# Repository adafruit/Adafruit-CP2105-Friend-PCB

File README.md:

## Adafruit CP2105 Friend - USB to Dual UART Serial Converters PCB

<a href="http://www.adafruit.com/products/6065"><br/>
Click here to purchase one from the Adafruit shop</a>

PCB files for the Adafruit CP2105 Friend - USB to Dual UART Serial Converters. 

Format is EagleCAD schematic and board layout
* https://www.adafruit.com/product/6065

### Description

On our first Pentium 120 tower (purchased at PCs for Everyone on Thorndike st in Cambridge Mass) came with two DE-9 serial ports on the back: COM1 and COM2. Perfect for connecting a mouse and maybe a modem. Nowadays, long gone are the days of parallel ports and serial ports. Now the USB port reigns supreme! But USB is hard, and you just want to transfer your every-day serial data from two serial ports to a single USB port without the complexity of a hub. What now? Enter the Adafruit CP2105 Friend!

The CP2105 is very similar to the CP2102N. Except, instead of having a single serial UART port, it has two. One is 'standard' and one is 'enhanced' - you'll get both enumerated when plugging in this device, without any hub required!

The Enhanced port can do:

* Data formats supported:
- Data bits: 5, 6, 7, and 8
- Stop bits: 1, 1.5, and 2
- Parity: odd, even, mark, space, no parity
* Baud rates: 300 bps to 2.0 Mbps
* 320 Byte receive and transmit buffers
* Modem control signals: CTS, RTS, DTR, DSR and RI

The Standard port can do:

* Data format: 8 data bits, 1 Stop bit
Parity: Even, Odd, No parity
* Baud rates: 2400 bps to 921600 bps
* 288 Byte receive and transmit buffers
* Modem control signals: CTS, RTS, DTR, DSR and RI

Like the CP2102N breakout, we have USB C connector and the same overall shape, but there are some significant changes. The pins are going to be totally different because we have two UARTs, one on either 'side' of the board. The left side is the Enhanced port, right side is the Standard port. We don't have extra GPIO pads and no indicator LEDs. Also the bottom row is a 'minimal' output of just the two RX/TX pads and power pins.

We like the CP210x series because it has better driver support than the CH340 and can do very high speeds, and variable speeds without stability issues. Compared to the FT232RL and FT231X, the CP210x has the same capabilities or better, at a great price! 

Each order comes with a fully assembled and tested board. We give you some pin header strip, solder it in to plug it into a breadboard and get access to all the pins.

For Linux you won't need a driver. For Windows, it will automatically grab the driver from Windows Update. For Mac OS X you can check out SiLabs driver page for the latest and greatest.

### License

Adafruit invests time and resources providing this open source design, please support Adafruit and open-source hardware by purchasing products from [Adafruit](https://www.adafruit.com)!

Designed by Limor Fried/Ladyada for Adafruit Industries.

Creative Commons Attribution/Share-Alike, all text above must be included in any redistribution. 
See license.txt for additional details.

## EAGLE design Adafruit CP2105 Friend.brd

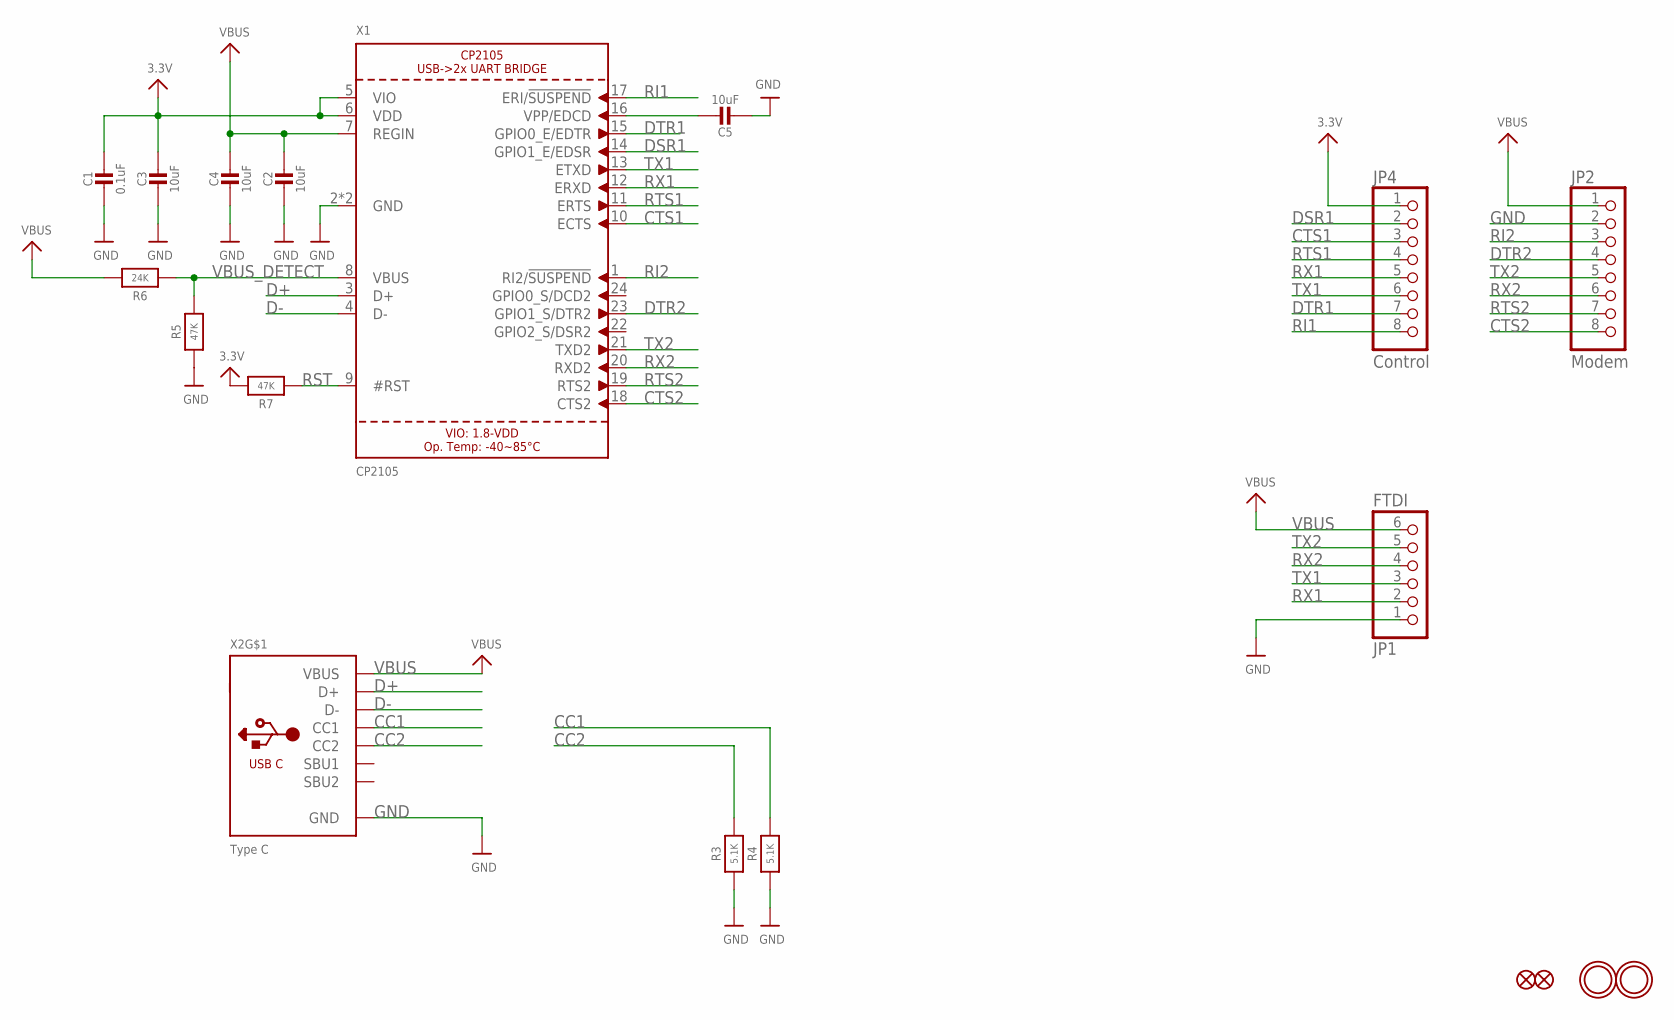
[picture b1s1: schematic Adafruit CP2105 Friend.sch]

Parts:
C1: 0.1uF; 0603-NO
C2, C3, C4, C5: 10uF; 0805-NO
FID1, FID2: FIDUCIAL_0.5MM
JP1: FTDI; 1X06_ROUND_70
JP2: Modem; 1X08_ROUND_70
JP4: Control; 1X08_ROUND_70
R3, R4: 5.1K; 0603-NO
R5, R7: 47K; 0603-NO
R6: 24K; 0603-NO
U$18, U$19: MOUNTINGHOLE2.0; MOUNTINGHOLE_2.0_PLATED
X1: CP2105; QFN24_4MM
X2: Type C; USB_C_CUSB31-CFM2AX-01-X

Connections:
3.3V: C1.1, C3.1, JP4.1, R7.2, X1.5 (VIO), X1.6 (VDD)
CC1: R4.2, X2.A5 (CC1)
CC2: R3.2, X2.B5 (CC2)
CTS1: JP4.3, X1.10 (ECTS)
CTS2: JP2.8, X1.18 (CTS2)
D+: X1.3 (D+), X2.A6 (D+), X2.B6 (D+)
D-: X1.4 (D-), X2.A7 (D-), X2.B7 (D-)
DSR1: JP4.2, X1.14 (GPIO1_E/EDSR)
DTR1: JP4.7, X1.15 (GPIO0_E/EDTR)
DTR2: JP2.4, X1.23 (GPIO1_S/DTR2)
GND: C1.2, C2.2, C3.2, C4.2, C5.2, JP1.1, JP2.2, R3.1, R4.1, R5.1, X1.2 (GND), X1.THERM (GND), X2.A1B12 (GND), X2.B1A12 (GND)
unnamed: C5.1, X1.16 (VPP/EDCD)
RI1: JP4.8, X1.17 (ERI/!SUSPEND)
RI2: JP2.3, X1.1 (RI2/!SUSPEND)
RST: R7.1, X1.9 (#RST)
RTS1: JP4.4, X1.11 (ERTS)
RTS2: JP2.7, X1.19 (RTS2)
RX1: JP1.2, JP4.5, X1.12 (ERXD)
RX2: JP1.4, JP2.6, X1.20 (RXD2)
TX1: JP1.3, JP4.6, X1.13 (ETXD)
TX2: JP1.5, JP2.5, X1.21 (TXD2)
VBUS: C2.1, C4.1, JP1.6, JP2.1, R6.2, X1.7 (REGIN), X2.A4B9 (VBUS), X2.B4A9 (VBUS)
VBUS_DETECT: R5.2, R6.1, X1.8 (VBUS)

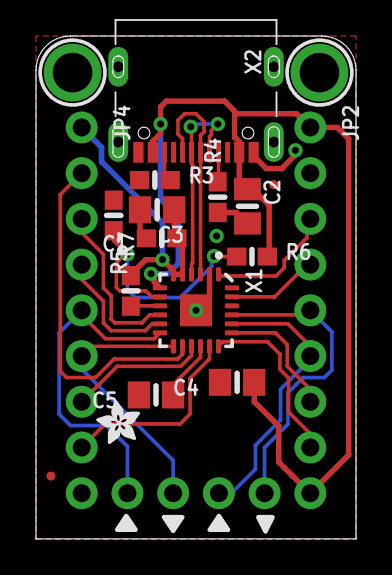
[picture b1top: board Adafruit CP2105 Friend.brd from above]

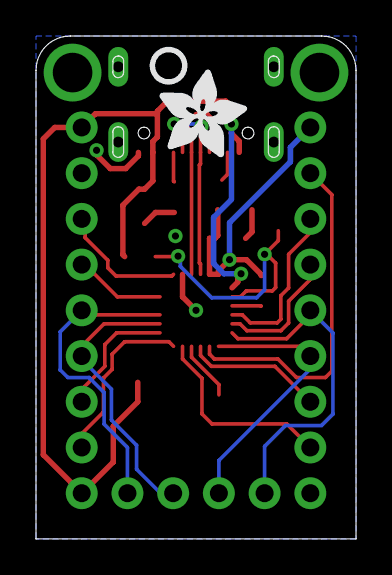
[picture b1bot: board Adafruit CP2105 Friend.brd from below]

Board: 2 copper layers, 17.8 x 27.9 mm, 48 parts (5 on the bottom side), 23 nets.

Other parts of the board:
PLABEL0: PLABEL0
PLABEL1: PLABEL1
PLABEL2: PLABEL2
PLABEL3: PLABEL3
PLABEL4: PLABEL4
PLABEL5: PLABEL5
PLABEL6: PLABEL6
PLABEL7: PLABEL7
PLABEL8: PLABEL8
PLABEL9: PLABEL9
PLABEL10: PLABEL10
PLABEL11: PLABEL11
PLABEL12: PLABEL12
PLABEL13: PLABEL13
PLABEL14: PLABEL14
PLABEL15: PLABEL15
PLABEL16: PLABEL16
PLABEL17: PLABEL17
PLABEL18: PLABEL18
PLABEL19: PLABEL19
PLABEL20: PLABEL20
PLABEL21: PLABEL21
PLABEL22: PLABEL22
PLABEL23: PLABEL23
PLABEL24: PLABEL24
PLABEL25: PLABEL25
U$8: ADAFRUIT_2.5MM
U$17: PCBFEAT-REV-040
U$22: ADAFRUIT_5MM

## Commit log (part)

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2024-10-24 cookiecutter

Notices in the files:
parts and their libraries:
microbuilder: This work is placed in the public domain, and may be freely used for commercial and non-commercial work with the following conditions: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
